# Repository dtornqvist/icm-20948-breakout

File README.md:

# Breakout board for ICM-20948 with i2c

This repository contains a breakout board for the 9-DOF Inertial Measurement Unit (IMU) from TDK, ICM-20948 ([data sheet](https://www.invensense.com/wp-content/uploads/2016/06/DS-000189-ICM-20948-v1.3.pdf)). The i2c communication pins and the interrupt pin has external connection. The board is designed for 3.3v power supply, as the IMU requires 1.8v IO-levels there is a voltage level translator that translate IO-levels to/from the supply voltage. As the voltage level translator contains internal pull up resistors, there is no need to have extra pull up resistors on the IO-lines.

### Note
I have done some initial tests of this board and it seems to work just fine. I have also done an [Arduino library](https://github.com/dtornqvist/icm-20948-arduino-library) for getting the data out.

## Bill of Material

- U1: NCP563SQ18T1G, 1.8v voltage regulator ([data sheet](https://www.onsemi.com/pub/Collateral/NCP562-D.PDF))
- U2: NTS0104, voltage level translator, ([data sheet](https://www.nxp.com/docs/en/data-sheet/NTS0104.pdf))
- U3: ICM-20948, IMU, ([data sheet](http://www.invensense.com/wp-content/uploads/2016/06/DS-000189-ICM-20948-v1.3.pdf))
- C1, C2, C3: Capacitor 0402, 0.1uF
- C4, C5: Capacitor 0402, 1.0uF
- J1, J2: 3-pin 0.1'/2.54mm connectors

## Repository Contents
- /Hardware - Eagle design files (.brd, .sch)

## License Information
The hardware is released under [Creative Commons Share-alike 3.0](http://creativecommons.org/licenses/by-sa/3.0/).

## Credits
Special thanks to [Kris Winer](https://github.com/kriswiner) for all helpful comments during the design process.

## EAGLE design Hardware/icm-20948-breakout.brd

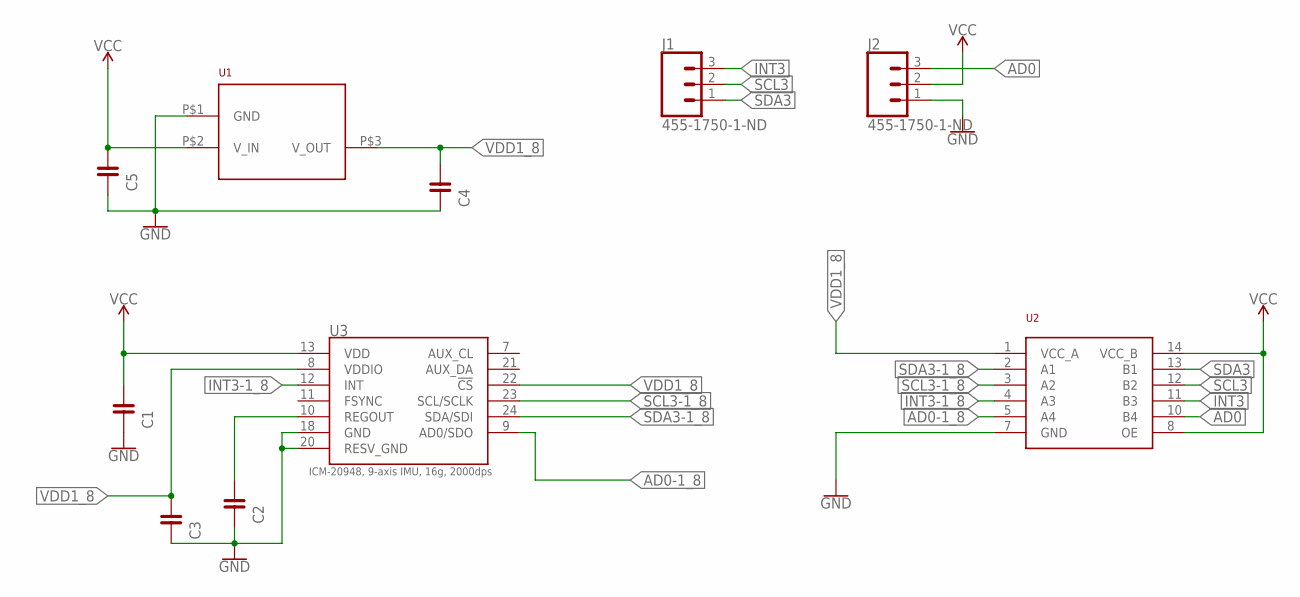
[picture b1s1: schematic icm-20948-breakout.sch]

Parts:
C1, C2, C3: 0.1uF; 0402
C4, C5: 1.0uF; 0402
J1, J2: 455-1750-1-ND; 1X03
U1: NCP563; SC−82AB
U2: NTS0104; SOT762-1
U3: ICM-20948; SPARKFUN-SENSORS_MPU-9250

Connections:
AD0: J2.3, U2.10 (B4)
AD0-1_8: U2.5 (A4), U3.9 (AD0/SDO)
GND: C1.P$2 (2), C2.P$2 (2), C3.P$2 (2), C4.P$2 (2), C5.P$2 (2), J2.1, U1.P$1 (GND), U2.7 (GND), U3.18 (GND), U3.20 (RESV_GND)
INT3: J1.3, U2.11 (B3)
INT3-1_8: U2.4 (A3), U3.12 (INT)
unnamed: C2.P$1 (1), U3.10 (REGOUT)
SCL3: J1.2, U2.12 (B2)
SCL3-1_8: U2.3 (A2), U3.23 (SCL/SCLK)
SDA3: J1.1, U2.13 (B1)
SDA3-1_8: U2.2 (A1), U3.24 (SDA/SDI)
VCC: C1.P$1 (1), C5.P$1 (1), J2.2, U1.P$2 (V_IN), U2.8 (OE), U2.14 (VCC_B), U3.13 (VDD)
VDD1_8: C3.P$1 (1), C4.P$1 (1), U1.P$3 (V_OUT), U2.1 (VCC_A), U3.8 (VDDIO), U3.22 (!CS)

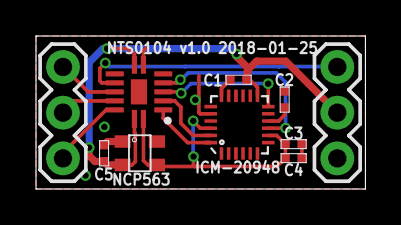
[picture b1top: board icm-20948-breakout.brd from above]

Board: 2 copper layers, 18.3 x 8.5 mm, 10 parts (0 on the bottom side), 12 nets.

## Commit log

2019-01-18 Initial commit.
2019-01-18 Connected unused io pins on the level translator to ground.
2019-01-18 Added question about clearance issue to readme.
2019-01-18 Minor updates to readme file.
2019-01-20 Redesign after comments. Changed footprints of capacitors. Removed routing under ICS. Connected nCS to level switcher to avoid a resistor. Added solder jumper to set address. Added ground planes on b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
2019-01-20 Updates to meet the design rules of OSH Park. However, still lots of clearance issues with the ICM-footprint.
2019-01-21 Updated ICM footprint. The design rules of OSH Park are now met.
2019-01-21 Fixed text layouts.
2019-01-21 Updated readme.
2019-01-21 Added gitignore and minor updates.
2019-01-22 Remake to fit 0.7 inch width.
2019-01-22 Changed DRC settings to get vias covered.
2019-01-23 Went back to 0.6 inch width. Took away ground plane under icm. Added AD0 as an output pin with pull-up and therefore removed solder jumper.
2019-01-23 Added label for the AD0 pin.
2019-01-24 Updated text sizes.
2019-01-25 Added production files.
2019-02-16 Updated readme with info about Arduino library.
2019-02-16 Added credits.

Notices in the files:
parts and their libraries:
SparkFun-Connectors: Licensing: Creative Commons ShareAlike 4.0 International - https://creativecommons.org/licenses/by-sa/4.0
FaBo-Capacitor: Released under the Creative Commons Attribution-ShareAlike 4.0 License
https://creativecommons.org/licenses/by-sa/4.0
